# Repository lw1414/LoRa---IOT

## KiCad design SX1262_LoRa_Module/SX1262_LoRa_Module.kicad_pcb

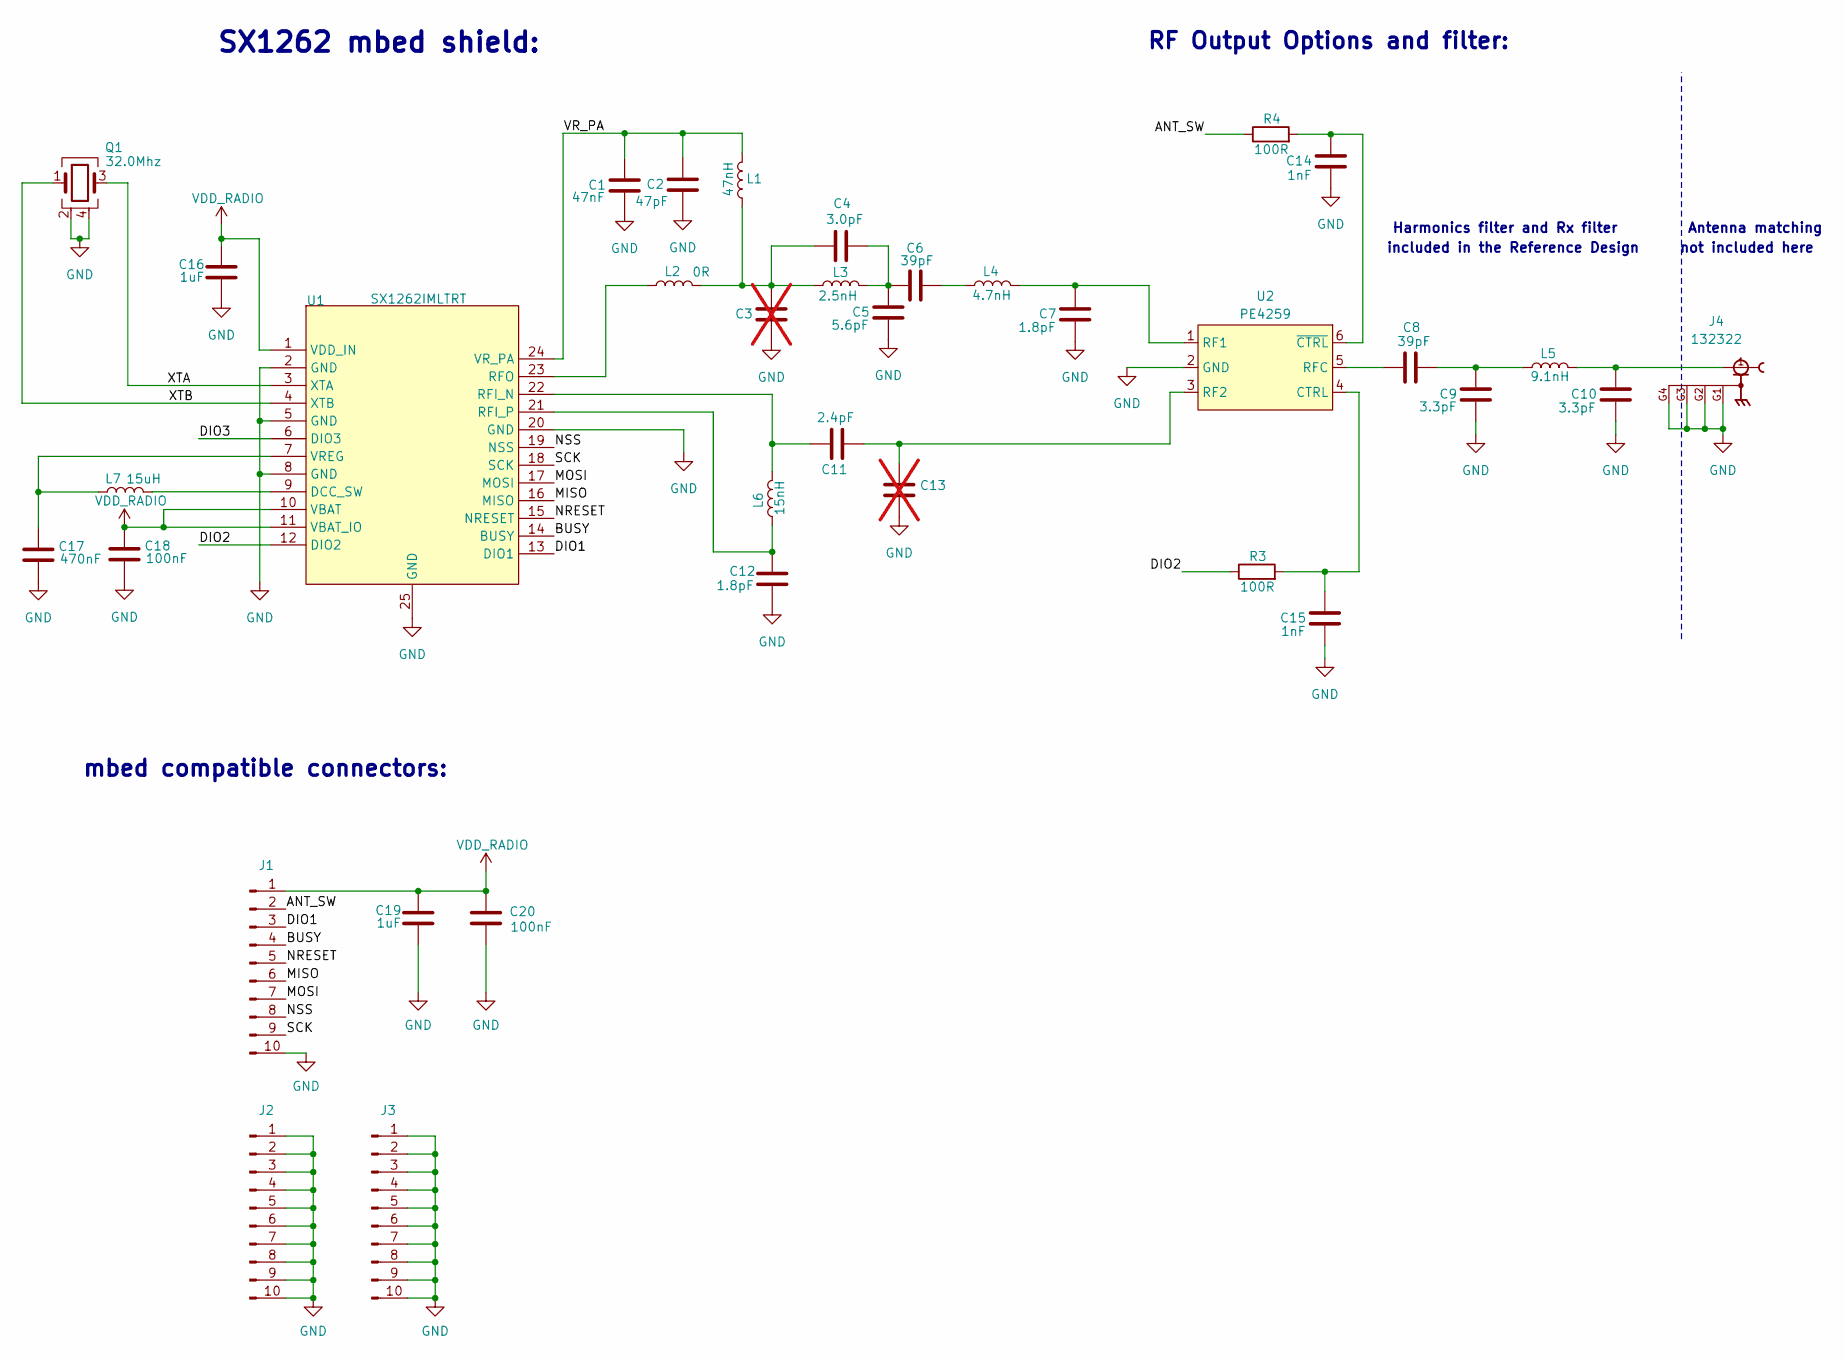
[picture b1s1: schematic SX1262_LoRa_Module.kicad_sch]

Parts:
C1: 47nF; C_0402_1005Metric; LCSC C307434
C2: 47pF; C_0402_1005Metric; LCSC C76970
C3, C13: C_0402_1005Metric; not fitted
C4: 3.0pF; C_0402_1005Metric; LCSC C88891
C5: 5.6pF; C_0402_1005Metric; LCSC C161329
C6, C8: 39pF; C_0402_1005Metric; LCSC C1563
C7, C12: 1.8pF; C_0402_1005Metric; LCSC C1553
C9, C10: 3.3pF; C_0402_1005Metric; LCSC C76906
C11: 2.4pF; C_0402_1005Metric; LCSC C48346
C14, C15: 1nF; C_0402_1005Metric; LCSC C189467
C16: 1uF; C_0402_1005Metric; LCSC C14445
C17: 470nF; C_0402_1005Metric; LCSC C92361
C18: 100nF; C_0402_1005Metric; LCSC C1525
C19: 1uF; C_0603_1608Metric; LCSC C53282223
C20: 100nF; C_0603_1608Metric
J1, J2, J3: Conn_01x10_Pin; PinHeader_1x10_P2.54mm_Vertical
J4: 132322; AMPHENOL_132322; MPN 132322
L1: 47nH; L_0402_1005Metric; LCSC C192855
L2: 0R; L_0402_1005Metric; LCSC C106231
L3: 2.5nH; L_0402_1005Metric; LCSC C703121
L4: 4.7nH; L_0402_1005Metric; LCSC C98064
L5: 9.1nH; L_0402_1005Metric; LCSC C6652904
L6: 15nH; L_0402_1005Metric; LCSC C91621
L7: 15uH; L0805; LCSC C383402
Q1: 32.0Mhz; CRYSTAL-SMD_4P-L2.0-W1.6-BL; LCSC C1986260
R3, R4: 100R; R_0402_1005Metric; LCSC C106232
U1: SX1262IMLTRT; QFN-24_L4.0-W4.0-P0.50-BL-EP2.6; LCSC C191341
U2: PE4259; SC-70-6_L2.2-W1.3-P0.65-LS2.1-BL; LCSC C470892

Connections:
/ANT_SW: J1.2, R4.1
/BUSY: J1.4, U1.14 (BUSY)
/DIO1: J1.3, U1.13 (DIO1)
/DIO2: R3.1, U1.12 (DIO2)
/DIO3: U1.6 (DIO3)
/MISO: J1.6, U1.16 (MISO)
/MOSI: J1.7, U1.17 (MOSI)
/NRESET: J1.5, U1.15 (NRESET)
/NSS: J1.8, U1.19 (NSS)
/SCK: J1.9, U1.18 (SCK)
/VR_PA: C1.2, C2.2, L1.2, U1.24 (VR_PA)
/XTA: Q1.3, U1.3 (XTA)
/XTB: Q1.1, U1.4 (XTB)
GND: C1.1, C2.1, C3.1, C5.1, C7.1, C9.1, C10.1, C12.2, C13.1, C14.1, C15.1, C16.2, C17.2, C18.2, C19.2, C20.2, J1.10, J2.1, J2.2, J2.3, J2.4, J2.5, J2.6, J2.7, J2.8, J2.9, J2.10, J3.1, J3.2, J3.3, J3.4, J3.5, J3.6, J3.7, J3.8, J3.9, J3.10, J4.G1, J4.G2, J4.G3, J4.G4, Q1.2, Q1.4, U1.2 (GND), U1.5 (GND), U1.8 (GND), U1.20 (GND), U1.25 (GND), U2.2 (GND); also elsewhere on the board
unnamed: C3.2, C4.2, L1.1, L2.2, L3.1
unnamed: C4.1, C5.2, C6.2, L3.2
unnamed: C6.1, L4.1
unnamed: C8.1, C9.2, L5.1
unnamed: C10.2, J4.1, L5.2
unnamed: L7.2, U1.9 (DCC_SW)
unnamed: C11.1, L6.2, U1.22 (RFI_N)
unnamed: C12.1, L6.1, U1.21 (RFI_P)
unnamed: L2.1, U1.23 (RFO)
unnamed: C17.1, L7.1, U1.7 (VREG)
unnamed: C15.2, R3.2, U2.4 (CTRL)
unnamed: C7.2, L4.2, U2.1 (RF1)
unnamed: C11.2, C13.2, U2.3 (RF2)
unnamed: C8.2, U2.5 (RFC)
unnamed: C14.2, R4.2, U2.6 (~CTRL)
VDD_RADIO: C16.1, C18.1, C19.1, C20.1, J1.1, U1.1 (VDD_IN), U1.10 (VBAT), U1.11 (VBAT_IO)

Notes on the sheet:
Antenna matching
RF Output Options and filter:
included in the Reference Design
Harmonics filter and Rx filter
not included here
SX1262 mbed shield:
mbed compatible connectors:

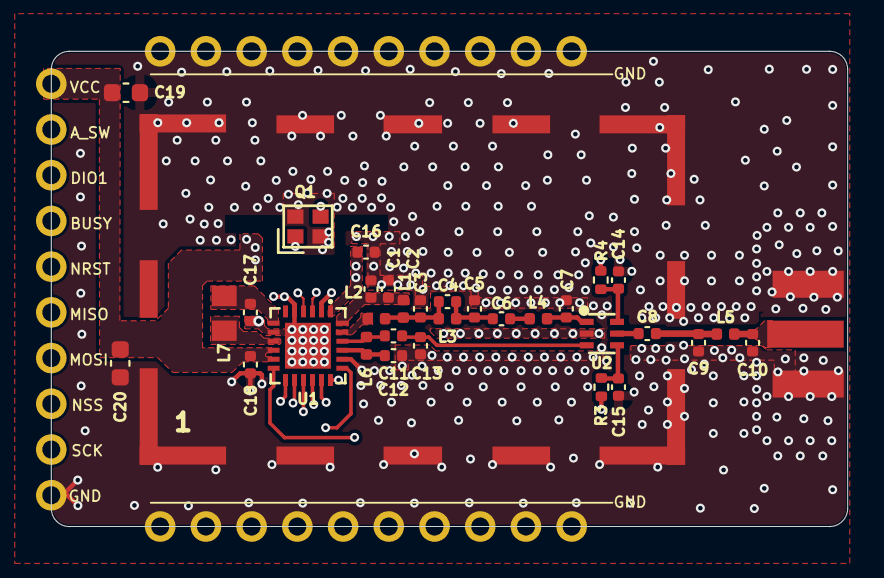
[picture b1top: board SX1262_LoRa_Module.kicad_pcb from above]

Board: 4 copper layers, 44.2 x 26.4 mm, 37 parts (0 on the bottom side), 29 nets.

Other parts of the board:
Shield: Logo symbol; BMIS-209-F - Shield

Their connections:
GND: Shield.1; also elsewhere on the board
